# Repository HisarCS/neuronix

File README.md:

electronics for neuronix, made in scotland

to fabricate the files use MODS CE https://modsproject.org/

some resources
- https://fabacademy.org/2019/docs/FabAcademy-Tutorials/week04_electronic_production/mods.html
- https://www.youtube.com/watch?v=ZbP9FEIVfaw&t=6225s

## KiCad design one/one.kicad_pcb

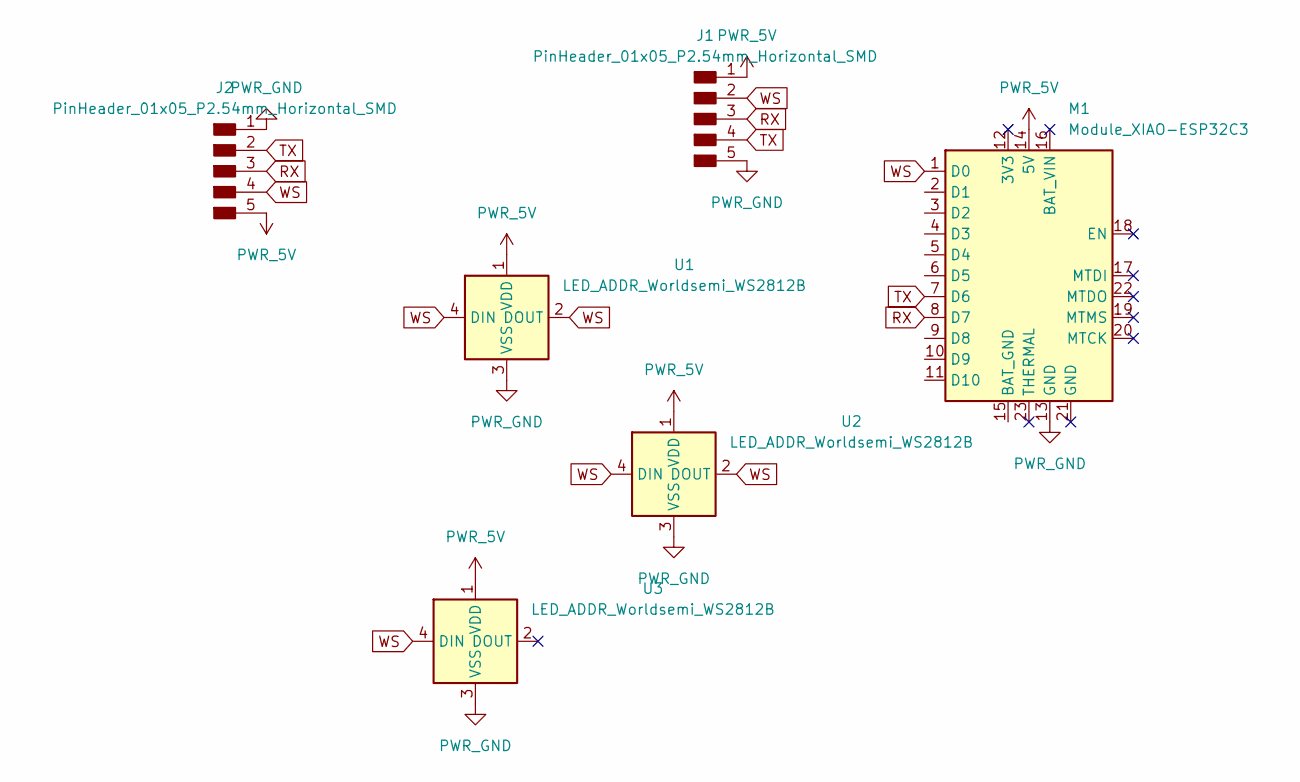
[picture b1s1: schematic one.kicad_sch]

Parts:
J1, J2: PinHeader_01x05_P2.54mm_Horizontal_SMD
M1: Module_XIAO-ESP32C3; Module_XIAO_Generic_SocketSMD
U1, U2, U3: LED_ADDR_Worldsemi_WS2812B

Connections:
PWR_5V: J1.1, J2.5, M1.14 (5V), U1.1 (VDD), U2.1 (VDD), U3.1 (VDD)
PWR_GND: J1.5, J2.1, M1.13 (GND), U1.3 (VSS), U2.3 (VSS), U3.3 (VSS)
RX: J1.3, J2.3, M1.8 (D7)
TX: J1.4, J2.2, M1.7 (D6)
WS: J1.2, J2.4, M1.1 (D0), U1.2 (DOUT), U1.4 (DIN), U2.2 (DOUT), U2.4 (DIN), U3.4 (DIN)

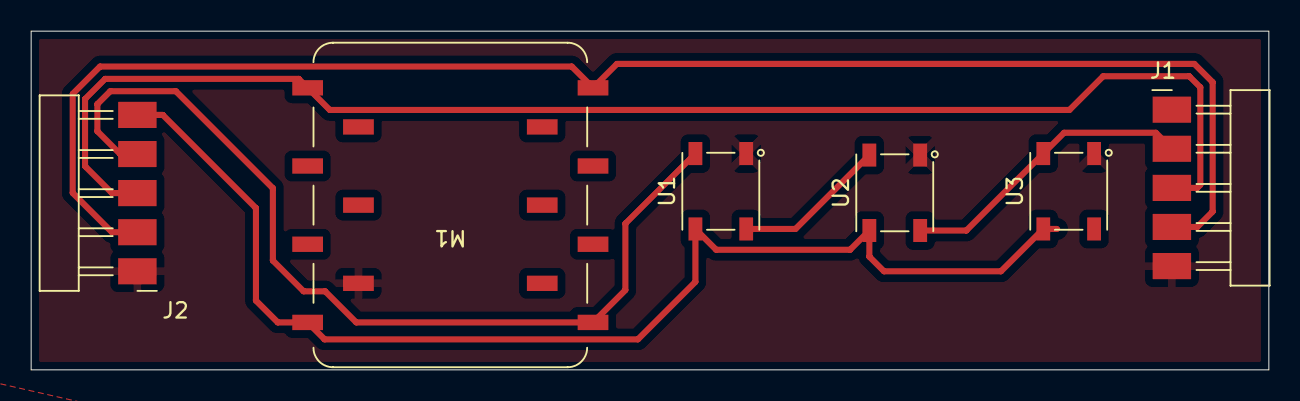
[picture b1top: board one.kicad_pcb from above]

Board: 2 copper layers, 80.4 x 22.0 mm, 6 parts (0 on the bottom side), 5 nets.

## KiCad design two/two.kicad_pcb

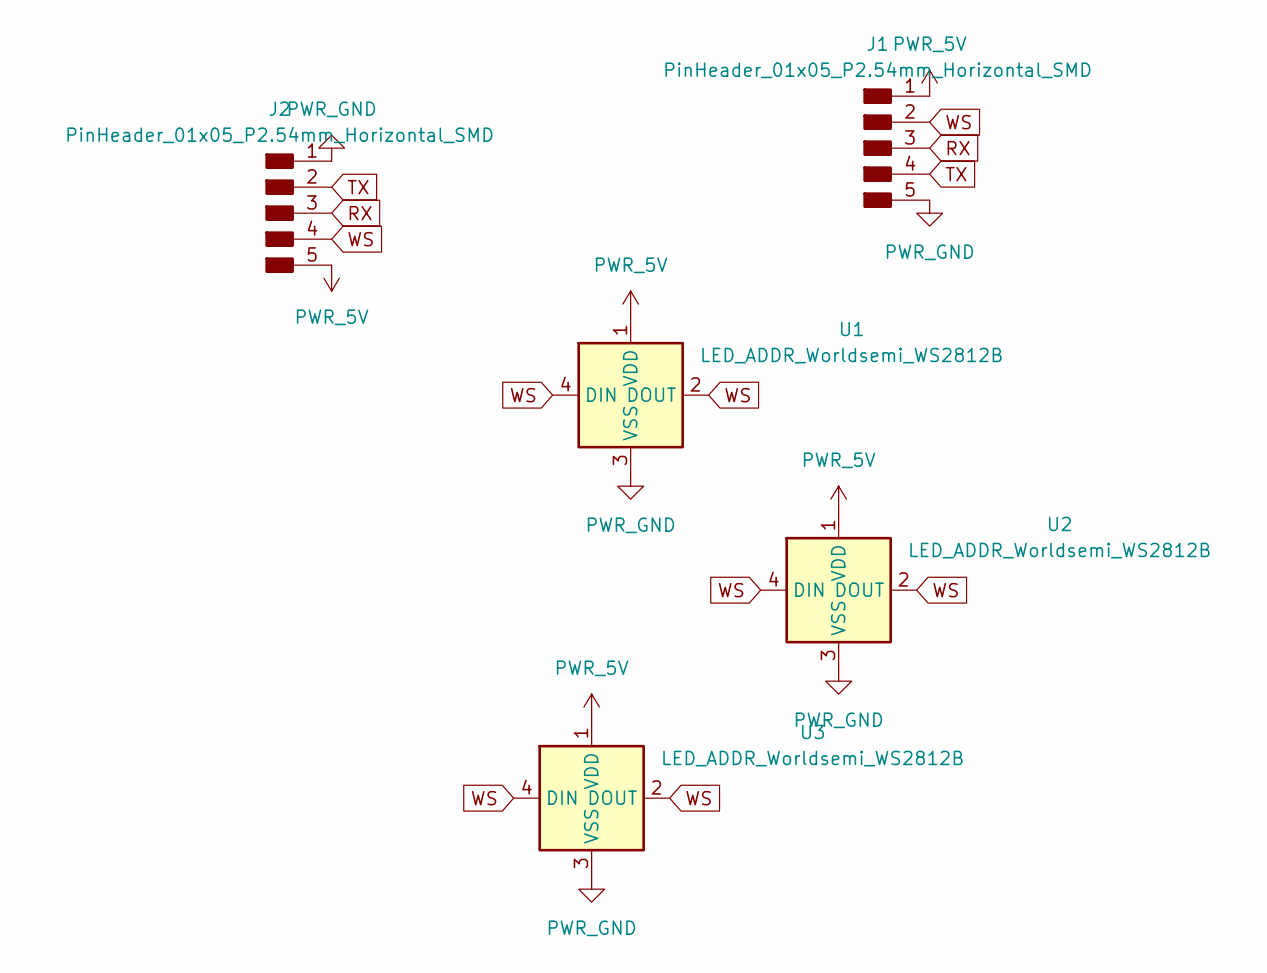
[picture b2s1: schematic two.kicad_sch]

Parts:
J1, J2: PinHeader_01x05_P2.54mm_Horizontal_SMD
U1, U2, U3: LED_ADDR_Worldsemi_WS2812B

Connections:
PWR_5V: J1.1, J2.5, U1.1 (VDD), U2.1 (VDD), U3.1 (VDD)
PWR_GND: J1.5, J2.1, U1.3 (VSS), U2.3 (VSS), U3.3 (VSS)
RX: J1.3, J2.3
TX: J1.4, J2.2
WS: J1.2, J2.4, U1.2 (DOUT), U1.4 (DIN), U2.2 (DOUT), U2.4 (DIN), U3.2 (DOUT), U3.4 (DIN)

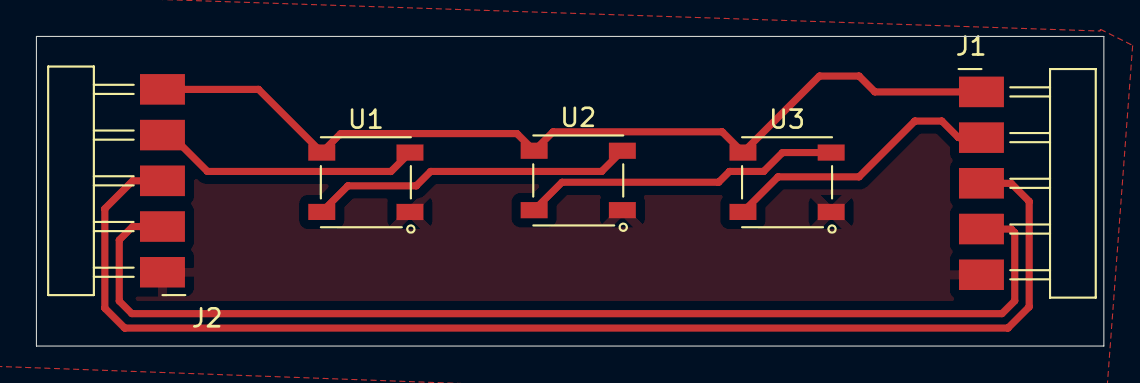
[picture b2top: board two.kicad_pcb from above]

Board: 2 copper layers, 59.3 x 17.2 mm, 5 parts (0 on the bottom side), 5 nets.

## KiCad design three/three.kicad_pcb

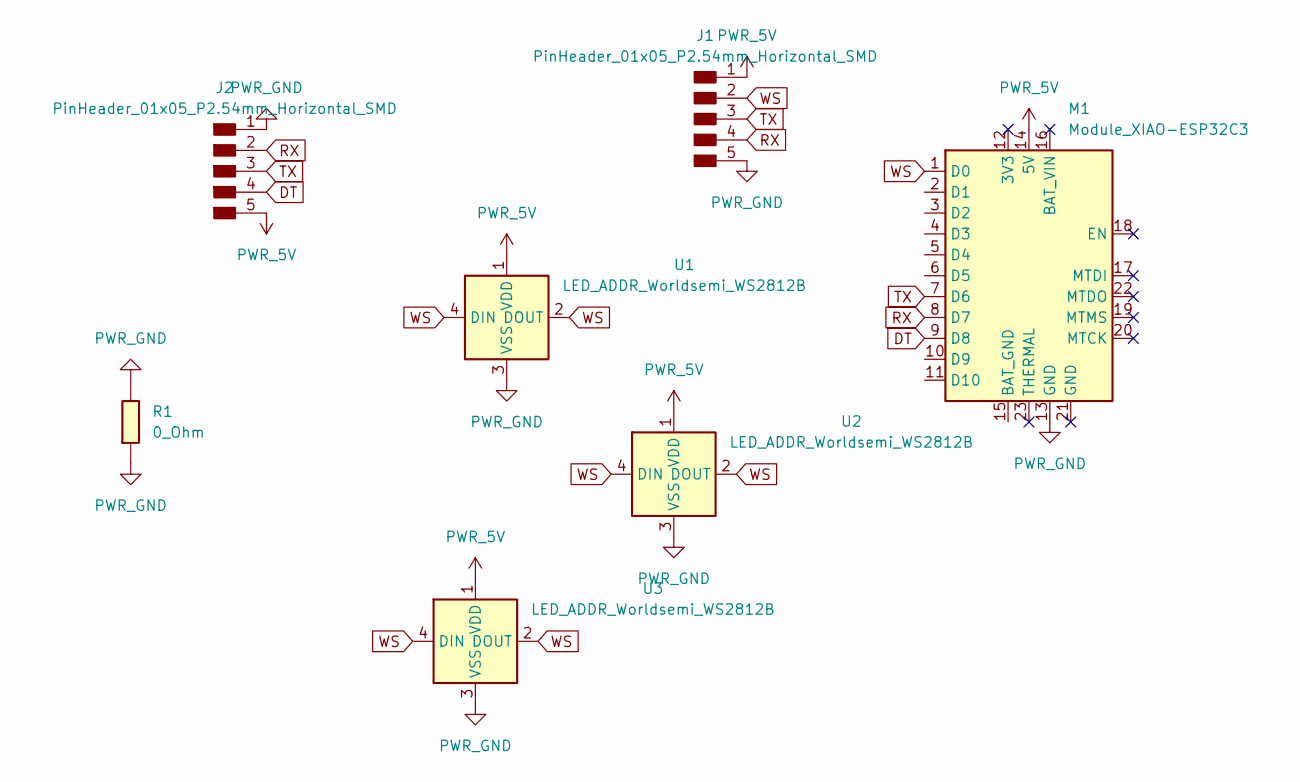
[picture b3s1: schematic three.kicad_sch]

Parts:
J1, J2: PinHeader_01x05_P2.54mm_Horizontal_SMD
M1: Module_XIAO-ESP32C3; Module_XIAO_Generic_SocketSMD
R1: 0_Ohm; R_1206
U1, U2, U3: LED_ADDR_Worldsemi_WS2812B

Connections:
DT: J2.4, M1.9 (D8)
PWR_5V: J1.1, J2.5, M1.14 (5V), U1.1 (VDD), U2.1 (VDD), U3.1 (VDD)
PWR_GND: J1.5, J2.1, M1.13 (GND), R1.1, R1.2, U1.3 (VSS), U2.3 (VSS), U3.3 (VSS)
RX: J1.4, J2.2, M1.8 (D7)
TX: J1.3, J2.3, M1.7 (D6)
WS: J1.2, M1.1 (D0), U1.2 (DOUT), U1.4 (DIN), U2.2 (DOUT), U2.4 (DIN), U3.2 (DOUT), U3.4 (DIN)

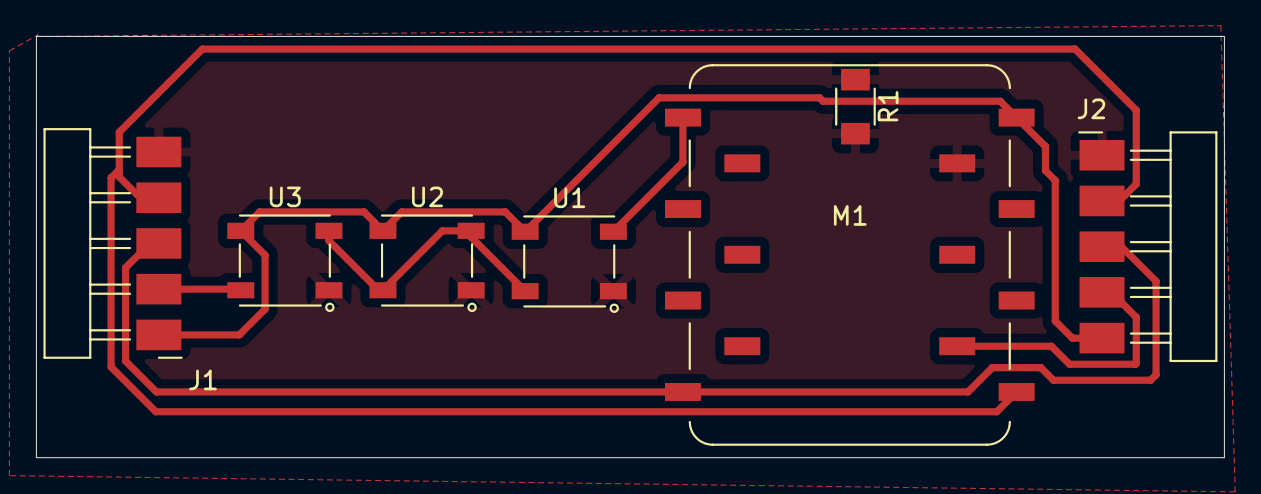
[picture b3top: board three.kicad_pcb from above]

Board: 2 copper layers, 66.0 x 23.4 mm, 7 parts (0 on the bottom side), 6 nets.
